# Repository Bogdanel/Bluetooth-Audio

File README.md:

Bluetooth to Audio using BK8000L Module

I designed the library for this module as I noticed there is none online yet.
I also added a board with the following functionalities missing:
- JTAG port
- Aux IN
- Reset switch

Documentation for board is taken from : http://www.electrodragon.com/w/BK8000L

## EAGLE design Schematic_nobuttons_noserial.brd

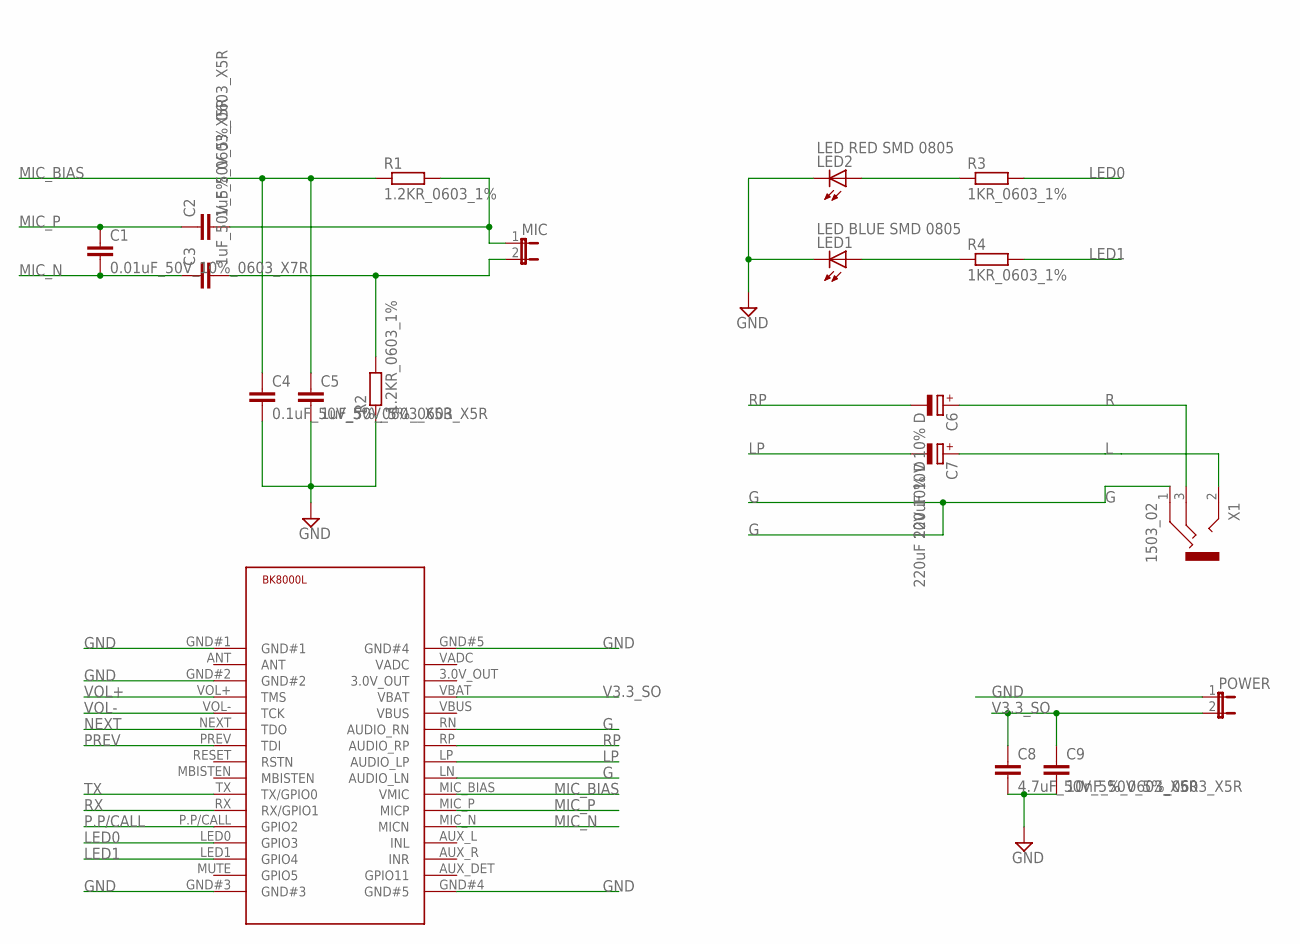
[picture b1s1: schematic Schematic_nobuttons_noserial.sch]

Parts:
C1: 0.01uF_50V_10%_0603_X7R; C0603
C2, C3, C5: 1uF_50V_5%_0603_X5R; C0603
C4: 0.1uF_50V_5%_0603_X5R; C0603
C6, C7: 220uF 10V 10% D; SMC_D
C8: 4.7uF_50V_5%_0603_X5R; C0603
C9: 10nF_50V_5%_0603_X5R; C0603
LED1: LED BLUE SMD 0805; CHIP-LED0805
LED2: LED RED SMD 0805; CHIP-LED0805
MIC: JP1E; JP1
POWER: JP1E; JP1
R1, R2: 1.2KR_0603_1%; R0603
R3, R4: 1KR_0603_1%; R0603
U$1: BK8000LBK8000L_PAD; BK8000L
X1: 1503_02

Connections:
G: U$1.LN (AUDIO_LN), U$1.RN (AUDIO_RN), X1.1
GND: C4.2, C5.2, C8.2, C9.2, LED1.C, LED2.C, POWER.1, R2.1, U$1.GND#1, U$1.GND#2, U$1.GND#3, U$1.GND#4 (GND#5), U$1.GND#5 (GND#4)
L: C7.+, X1.2
LED0: R3.2, U$1.LED0 (GPIO3)
LED1: R4.2, U$1.LED1 (GPIO4)
LP: C7.-, U$1.LP (AUDIO_LP)
MIC_BIAS: C4.1, C5.1, R1.1, U$1.MIC_BIAS (VMIC)
MIC_N: C1.2, C3.1, U$1.MIC_N (MICN)
MIC_P: C1.1, C2.1, U$1.MIC_P (MICP)
unnamed: LED1.A, R4.1
unnamed: LED2.A, R3.1
unnamed: C3.2, MIC.2, R2.2
unnamed: C2.2, MIC.1, R1.2
NEXT: U$1.NEXT (TDO)
P.P/CALL: U$1.P.P/CALL (GPIO2)
PREV: U$1.PREV (TDI)
R: C6.+, X1.3
RP: C6.-, U$1.RP (AUDIO_RP)
RX: U$1.RX (RX/GPIO1)
TX: U$1.TX (TX/GPIO0)
V3.3_SO: C8.1, C9.1, POWER.2, U$1.VBAT
VOL+: U$1.VOL+ (TMS)
VOL-: U$1.VOL- (TCK)

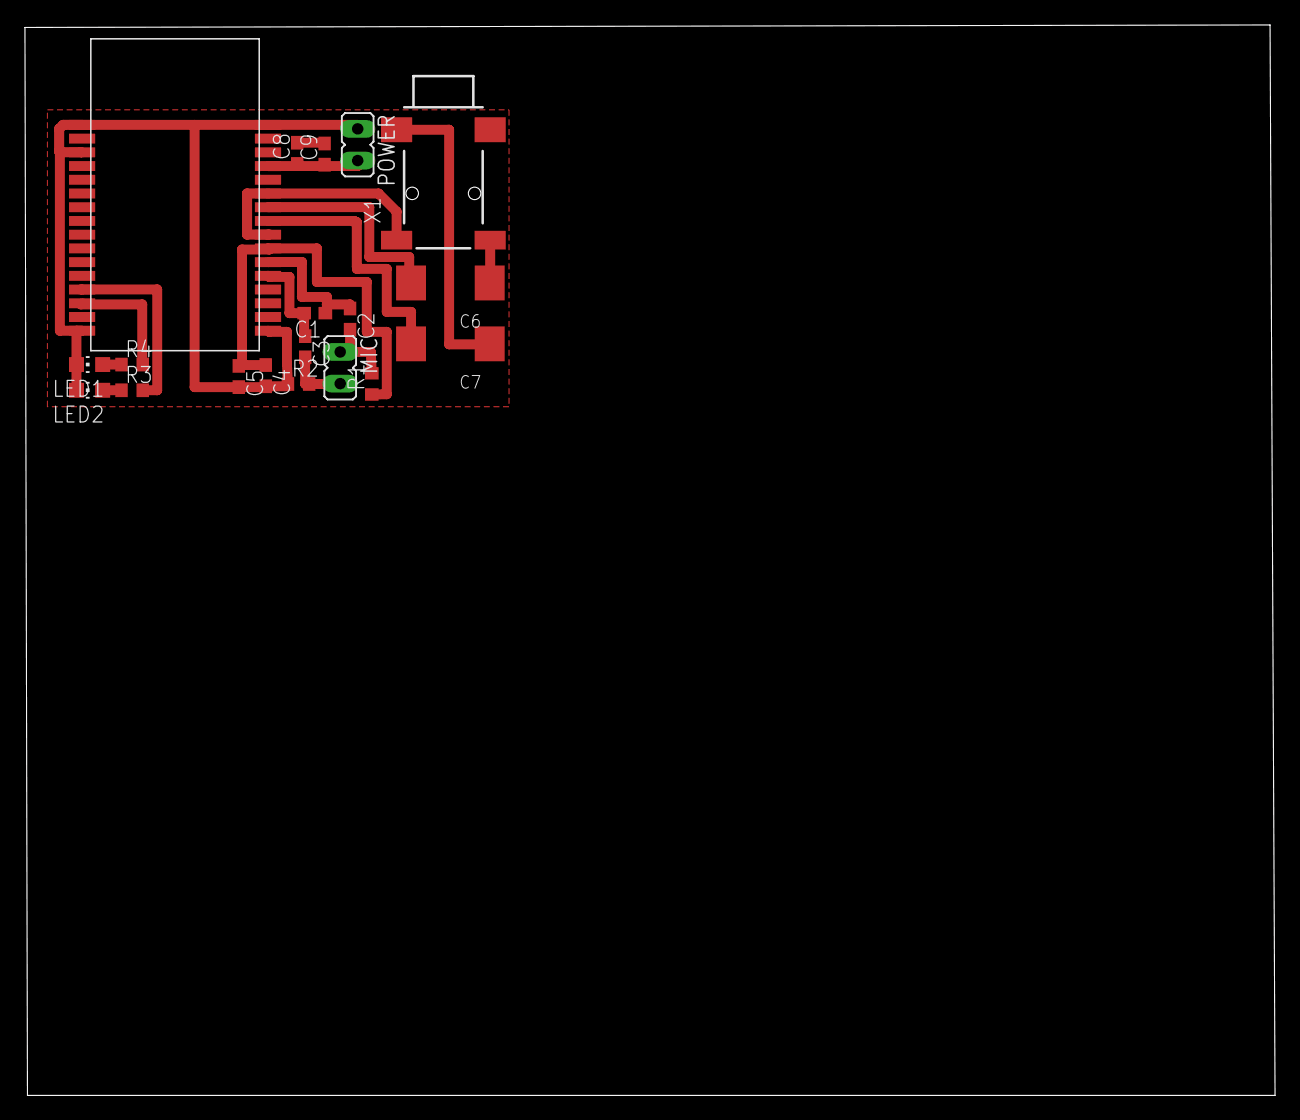
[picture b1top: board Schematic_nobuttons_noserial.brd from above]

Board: 2 copper layers, 100.2 x 85.8 mm, 19 parts (0 on the bottom side), 16 nets.

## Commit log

2017-07-27 Add the readme file
2017-07-27 Move libs into one folder
2017-07-28 Boards pdf for print
2017-08-04 updated library pads position to go a bit under the module so they can be soldered easier
